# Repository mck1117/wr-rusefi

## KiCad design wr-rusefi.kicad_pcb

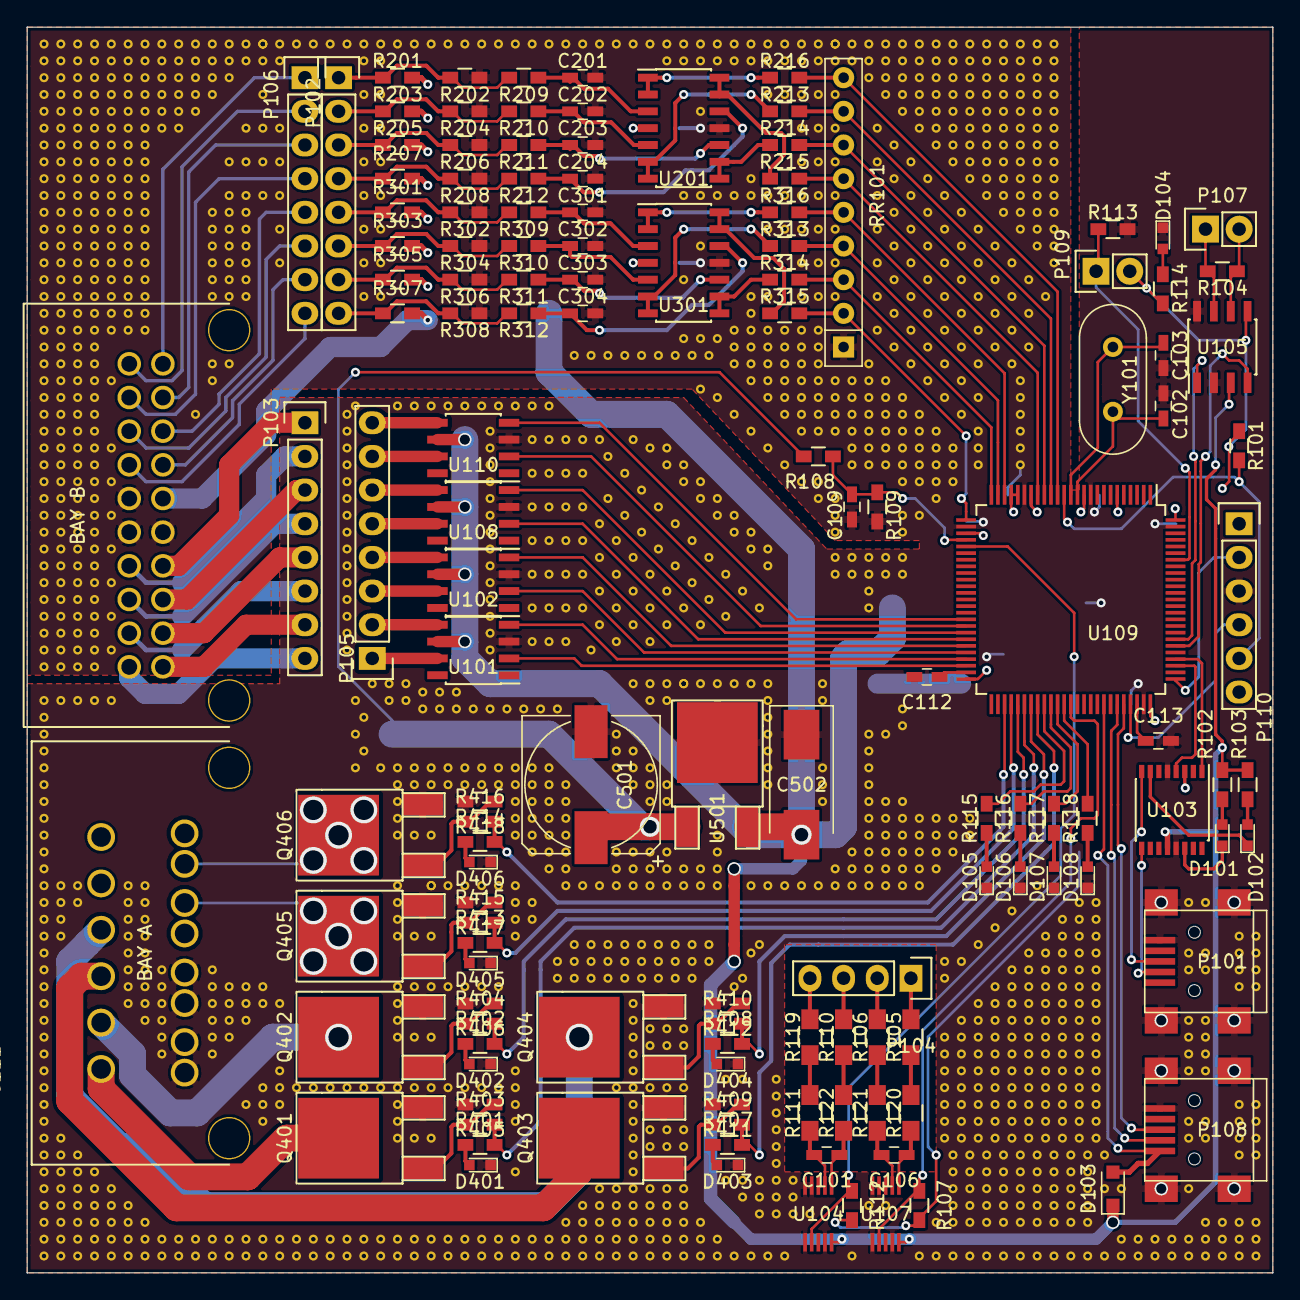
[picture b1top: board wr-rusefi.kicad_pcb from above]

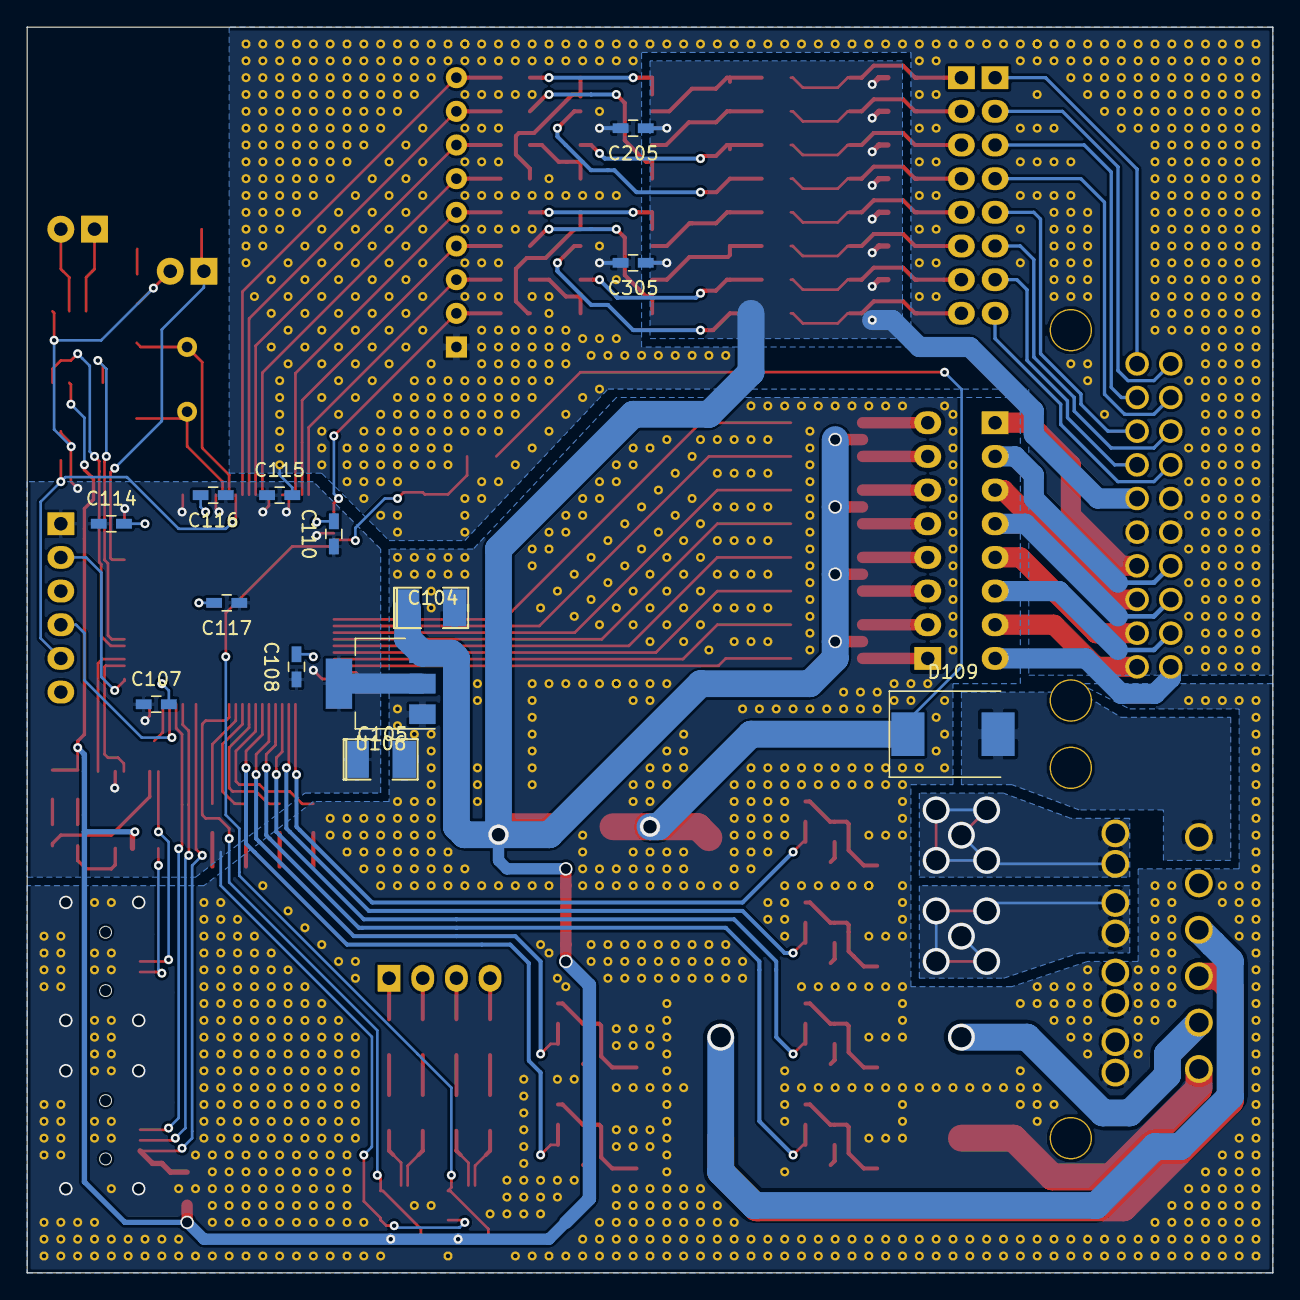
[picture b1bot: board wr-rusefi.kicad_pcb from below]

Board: 2 copper layers, 94.0 x 94.0 mm, 147 parts (13 on the bottom side), 140 nets.

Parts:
C101, C106: 1nF; C_0603_HandSoldering
C102, C103: 20pF; C_0603_HandSoldering
C104: CP; SMD-1210_Pol
C105: 22uF; SMD-1210_Pol
C107, C108, C114, C115, C116: .1uF; C_0603_HandSoldering
C109, C201, C202, C203, C204, C301, C302, C303, C304: 0.01uF; C_0603_HandSoldering
C110, C117: 4.7uF; C_0603_HandSoldering
C111: MOLEX_34703_2012; MOLEX_34707-2012
C112, C113: 2.2uF; C_0603_HandSoldering
C205, C305: 0.1uF; C_0603_HandSoldering
C501: 330uF; CP_Elec_10x10
C502: 220uF; CP_Tantalum_Case-D_EIA-7343-31_Hand
D101, D102, D104, D105, D106, D107, D108, D401, D402, D403, D404, D405, D406: LED; LED_0603
D103: PMEG2010EA; D_SOD-323_HandSoldering
D109: D_Schottky; D_SMC_Standard
P101, P108: USB_OTG; USB_Mini-B
P102, P103, P105, P106: CONN_01X08; Socket_Strip_Straight_1x08
P104: CONN_01X04; Socket_Strip_Straight_1x04
P107, P109: CONN_01X02; Socket_Strip_Straight_1x02
P110: CONN_01X06; Socket_Strip_Straight_1x06
Q401, Q402, Q403, Q404, Q405, Q406: IRF540N; TO-252-2Lead
R101, R107, R109, R112, R113, R209, R210, R211, R212, R309, R310, R311, R312: 10k; R_0603_HandSoldering
R102, R103, R114, R115, R116, R117, R118, R401, R402, R407, R408, R413, R414: 1k; R_0603_HandSoldering
R104: 120; R_0603_HandSoldering
R105, R106, R110, R111, R119, R120, R121, R122: 5k; R_0805_HandSoldering
R108: 100k; R_0603_HandSoldering
R201, R202, R203, R204, R205, R206, R207, R208, R301, R302, R303, R304, R305, R306, R307, R308: R; R_0603_HandSoldering
R213, R214, R215, R216, R313, R314, R315, R316: 1500; R_0603_HandSoldering
R403, R404, R409, R410, R415, R416: 20; R_0603_HandSoldering
R405, R406, R411, R412, R417, R418: 20k; R_0603_HandSoldering
RR101: RR8; R_Array_SIP9
U101, U102, U108, U110: ISL89410; SOIC-8_3.9x4.9mm_Pitch1.27mm
U103: FT230XS; SSOP-16_4.4x5.2mm_Pitch0.65mm
U104, U107: MAX9924; uMAX-10
U105: MCP2562-E/SN; SOIC-8_3.9x4.9mm_Pitch1.27mm
U106: LD1117S33TR; SOT-223
U109: STM32F407VGTx; LQFP-100_14x14mm_Pitch0.5mm
U201, U301: LM324; SOIC-14_3.9x8.7mm_Pitch1.27mm
U501: LM7805CT; TO-252-2Lead
Y101: Crystal; Crystal_HC49-U_Vertical

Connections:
+3V3: C105.1, C107.1, C108.1, C110.1, C114.1, C115.1, C116.1, C117.1, P109.2, P110.1, R101.1, R107.2, R112.2, R114.2, U103.3, U105.5, U106.2, U109.6, U109.11, U109.19, U109.21, U109.22, U109.28, U109.50, U109.75, U109.100
+5V: C104.1, C111.26, C205.1, C305.1, C502.2, D103.1, R102.2, R103.2, R201.2, R203.2, R205.2, R207.2, R301.2, R303.2, R305.2, R307.2, U101.6, U102.6, U103.12, U104.10, U105.3, U106.3, U107.10, U108.6, U110.6, U201.4, U301.4, U501.3
+12V: C501.1, D109.1, R108.2, U501.1
AIN0: P102.1, R201.1, R202.2, R209.2
AIN1: P102.2, R203.1, R204.2, R210.2
AIN2: P102.3, R205.1, R206.2, R211.2
AIN3: P102.4, R207.1, R208.2, R212.2
AIN4: P102.5, R301.1, R302.2, R309.2
AIN5: P102.6, R303.1, R304.2, R310.2
AIN6: P102.7, R305.1, R306.2, R311.2
AIN7: P102.8, R307.1, R308.2, R312.2
BATT_ADC: C109.1, R108.1, R109.2, U109.29
CANH: P107.1, R104.2, U105.7
CANL: P107.2, R104.1, U105.6
CAN_RX: U105.4, U109.81
CAN_TX: U105.1, U109.82
GND: C102.2, C103.2, C104.2, C105.2, C107.2, C108.2, C109.2, C110.2, C111.7, C111.8, C111.15, C111.16, C111.25, C112.2, C113.2, C114.2, C115.2, C116.2, C117.2, C201.2, C202.2, C203.2, C204.2, C205.2, C301.2, C302.2, C303.2, C304.2, C305.2, C501.2, C502.1, D104.1, D105.1, D106.1, D107.1, D108.1, D401.1, D402.1, D403.1, D404.1, D405.1, D406.1, P101.5, P101.6, P108.5, P108.6, P110.3, Q401.3, Q402.3, Q403.3, Q404.3, Q405.3, Q406.3, R109.1, R113.2, R202.1, R204.1, R206.1, R208.1, R302.1, R304.1, R306.1, R308.1, R405.2, R406.2, R411.2, R412.2, R417.2, R418.2, RR101.1, U101.3, U102.3, U103.5, U103.13, U104.4, U104.5, U104.6, U104.9, U105.2, U105.8, U106.1, U107.4, U107.5, U107.6, U107.9, U108.3, U109.10, U109.20, U109.27, U109.74, U109.99, U110.3, U201.11, U301.11, U501.2
IGN_A_IN: U101.2, U109.48
IGN_A_OUT: P105.1, U101.7
IGN_B_IN: U101.4, U109.47
IGN_B_OUT: P105.2, U101.5
IGN_C_IN: U102.2, U109.46
IGN_C_OUT: P105.3, U102.7
IGN_D_IN: U102.4, U109.45
IGN_D_OUT: P105.4, U102.5
IGN_E_IN: U108.2, U109.44
IGN_E_OUT: P105.5, U108.7
IGN_F_IN: U108.4, U109.43
IGN_F_OUT: P105.6, U108.5
IGN_G_IN: U109.42, U110.2
IGN_G_OUT: P105.7, U110.7
IGN_H_IN: U109.41, U110.4
IGN_H_OUT: P105.8, U110.5
INJ_A_IN: R413.2, R415.2, U109.54
INJ_B_IN: R414.2, R416.2, U109.53
NRST: P110.5, R101.2, U109.14
unnamed: C101.1, R122.1, U104.1
unnamed: C101.2, R111.1, U104.2
unnamed: C102.1, U109.12, Y101.2
unnamed: C103.1, U109.13, Y101.1
unnamed: C106.1, R120.1, U107.1
unnamed: C106.2, R121.1, U107.2
unnamed: C111.6, D109.2
unnamed: C111.11, P103.8
unnamed: C111.12, P103.6
unnamed: C111.13, P103.4
unnamed: C111.14, P103.2
unnamed: C111.17, P106.8
unnamed: C111.18, P106.6
unnamed: C111.19, P106.4
unnamed: C111.20, P106.2
unnamed: C111.21, P103.7
unnamed: C111.22, P103.5
unnamed: C111.23, P103.3
unnamed: C111.24, P103.1
unnamed: C111.27, P106.7
unnamed: C111.28, P106.5
unnamed: C111.29, P106.3
unnamed: C111.30, P106.1
unnamed: C112.1, U109.49
unnamed: C113.1, U109.73
unnamed: C201.1, R209.1, U201.3
unnamed: C202.1, R210.1, U201.5
unnamed: C203.1, R211.1, U201.10
unnamed: C204.1, R212.1, U201.12
unnamed: C301.1, R309.1, U301.3
unnamed: C302.1, R310.1, U301.5
unnamed: C303.1, R311.1, U301.10
unnamed: C304.1, R312.1, U301.12
unnamed: D101.1, U103.14
unnamed: D101.2, R102.1
unnamed: D102.1, U103.7
unnamed: D102.2, R103.1
unnamed: D104.2, R114.1
unnamed: D105.2, R115.1
unnamed: D106.2, R116.1
unnamed: D107.2, R117.1
unnamed: D108.2, R118.1
unnamed: D401.2, R401.1
unnamed: D402.2, R402.1
unnamed: D403.2, R407.1
unnamed: D404.2, R408.1
unnamed: D405.2, R413.1
unnamed: D406.2, R414.1
unnamed: P101.2, U103.9
unnamed: P101.3, U103.8
unnamed: P109.1, R113.1, U109.94
unnamed: Q401.1, R403.1, R405.1
unnamed: Q402.1, R404.1, R406.1
unnamed: Q403.1, R409.1, R411.1
unnamed: Q404.1, R410.1, R412.1
unnamed: Q405.1, R415.1, R417.1
unnamed: Q406.1, R416.1, R418.1
unnamed: R105.1, R120.2
unnamed: R106.1, R121.2
unnamed: R110.1, R122.2
unnamed: R111.2, R119.1
unnamed: R213.1, U201.6, U201.7
unnamed: R214.1, U201.8, U201.9
unnamed: R215.1, U201.13, U201.14
unnamed: R216.1, U201.1, U201.2
unnamed: R313.1, U301.6, U301.7
unnamed: R314.1, U301.8, U301.9
unnamed: R315.1, U301.13, U301.14
unnamed: R316.1, U301.1, U301.2
PD12: R115.2, U109.59
PD13: R116.2, U109.60
PD14: R117.2, U109.61
PD15: R118.2, U109.62
SWCLK: P110.2, U109.76
SWDIO: P110.4, U109.72
USB_DM: P108.2, U109.70
USB_DP: P108.3, U109.71
VBUS: D103.2, P108.1, U109.68
VR1+: P104.1, R105.2
VR1-: P104.2, R106.2
VR2+: P104.3, R110.2
VR2-: P104.4, R119.2
VRIN1: R107.1, U107.7, U109.63
VRIN2: R112.1, U104.7, U109.30
a0: R216.2, RR101.9, U109.15
a1: R213.2, RR101.8, U109.16
a2: R214.2, RR101.7, U109.17
a3: R215.2, RR101.6, U109.18
a4: R316.2, RR101.5, U109.23
a5: R313.2, RR101.4, U109.24
a6: R314.2, RR101.3, U109.25
a7: R315.2, RR101.2, U109.26
ftdi_rx: U103.4, U109.78
ftdi_tx: U103.1, U109.79
inj_a: C111.9, Q405.2
inj_b: C111.10, Q406.2
ls_1: R401.2, R403.2, U109.56
ls_2: R402.2, R404.2, U109.55
ls_3: R407.2, R409.2, U109.58
ls_4: R408.2, R410.2, U109.57
ls_out_1: C111.1, Q401.2
ls_out_2: C111.2, Q402.2
ls_out_3: C111.3, Q403.2
ls_out_4: C111.4, Q404.2

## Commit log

2017-01-24 Add gitignore
2017-01-24 Add files from old wr-efi-motherboard
2017-01-24 Rename design files
2017-01-24 Fix library name
2017-01-24 Fix library linkages
2017-01-26 Rework most of board for rusefi
2017-01-30 Board mostly complete
2017-01-30 Add debug LEDs, power via 2nd USB
2017-01-30 Shrink, place all silk text
2017-01-30 cleanup
2017-01-30 Add reverse protection diode, board cleanup
2017-01-31 minor layout
2017-01-31 start redoing layout, lowside drivers and analog routed
2017-02-01 Mostly done new layout
2017-02-01 Add rear ground pour
2017-02-03 Rough placement of reset & boot0 pullups and jumper
2017-02-15 Move CAN to PD0/1, nearly done routing
2017-02-25 Via stitching bonanza
2017-02-26 more vias
2017-02-27 more via stitch
2017-02-28 erc & drc
